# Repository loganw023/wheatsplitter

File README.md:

# wheatsplitter
This is a custom split ortholinear mechanical keyboard. I built this project to qualify for Outpost and to further my PCB, CAD, and coding skills. I was also interested in building this keyboard because I worked on Hackpad last summer, and wanted to continue building keyboard-type projects. This project taught me a lot about PCB design, especially since my last PCB was done in December. I also learned a lot about the specifics on how keyboard matrixes work, which was very interesting. 

## Schematic
Here is my schematic:

## PCB
Here is the PCB:

## CAD
Here is the CAD for the case:

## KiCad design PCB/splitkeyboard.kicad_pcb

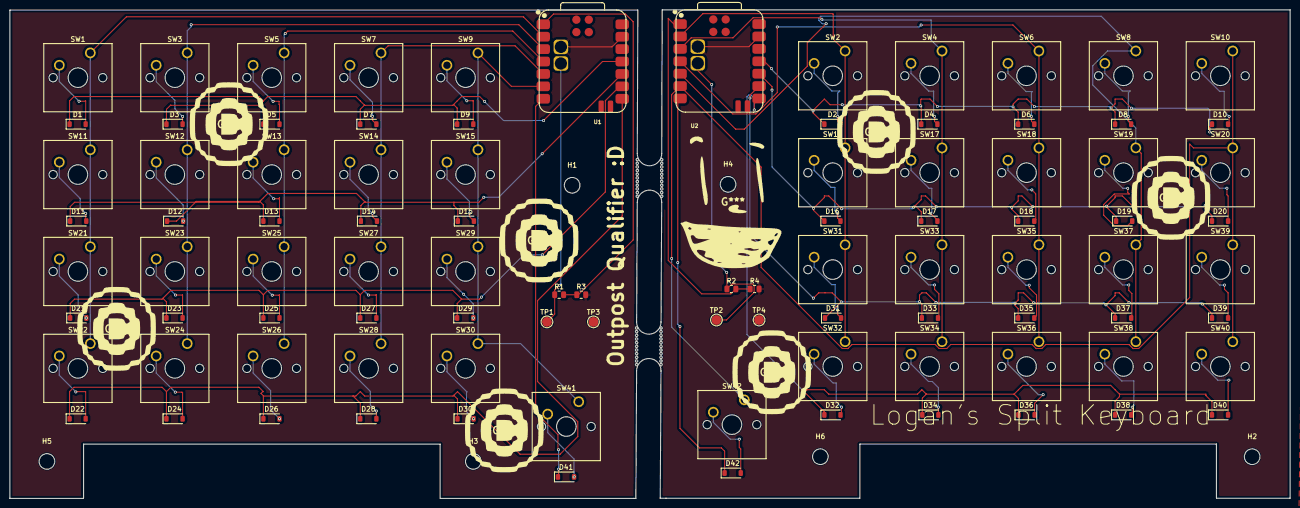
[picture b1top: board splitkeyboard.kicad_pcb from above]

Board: 2 copper layers, 262.1 x 100.0 mm, 102 parts (0 on the bottom side), 67 nets.

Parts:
D1, D2, D3, D4, D5, D6, D7, D8, D9, D10, D11, D12, D13, D14, D15, D16, D17, D18, D19, D20, D21, D22, D23, D24, D25, D26, D27, D28, D29, D30, D31, D32, D33, D34, D35, D36, D37, D38, D39, D40, D41, D42: D; D_SOD-123
H1, H2, H3, H4, H5, H6: MountingHole; MountingHole_3.2mm_M3
H4#2, H7: MountingHole; mouse-bite-5mm-slot
R1, R2: 806k; R_0805_2012Metric
R3, R4: 2M; R_0805_2012Metric
SW1, SW2, SW3, SW4, SW5, SW6, SW7, SW8, SW9, SW10, SW11, SW12, SW13, SW14, SW15, SW16, SW17, SW18, SW19, SW20, SW21, SW22, SW23, SW24, SW25, SW26, SW27, SW28, SW29, SW30, SW31, SW32, SW33, SW34, SW35, SW36, SW37, SW38, SW39, SW40, SW41, SW42: SW_Push; SW_Cherry_MX_1.00u_PCB
TP1, TP2, TP3, TP4: TestPoint; TestPoint_Pad_D2.0mm
U1, U2: XIAO-nRF52840-SMD; modified-XIAO-nRF52840-SMD

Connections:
/Left/BT_PIN: R1.2, R3.1, U1.1 (P0.02_A0_D0)
/Left/COL0: SW1.1, SW11.1, SW21.1, SW22.1, U1.2 (P0.03_A1_D1)
/Left/COL1: SW3.1, SW12.1, SW23.1, SW24.1, U1.3 (P0.28_A2_D2)
/Left/COL2: SW5.1, SW13.1, SW25.1, SW26.1, U1.4 (P0.29_A3_D3)
/Left/COL3: SW7.1, SW14.1, SW27.1, SW28.1, U1.5 (P0.04_A4_D4_SDA)
/Left/COL4: SW9.1, SW15.1, SW29.1, SW30.1, SW41.1, U1.6 (P0.05_A5_D5_SCL)
/Left/ROW0: D1.1 (K), D3.1 (K), D5.1 (K), D7.1 (K), D9.1 (K), U1.11 (P1.15_D10_MOSI)
/Left/ROW1: D11.1 (K), D12.1 (K), D13.1 (K), D14.1 (K), D15.1 (K), U1.10 (P1.14_D9_MISO)
/Left/ROW2: D21.1 (K), D23.1 (K), D25.1 (K), D27.1 (K), D29.1 (K), U1.9 (P1.13_D8_SCK)
/Left/ROW3: D22.1 (K), D24.1 (K), D26.1 (K), D28.1 (K), D30.1 (K), U1.8 (P1.12_D7_RX)
/Left/ROW4: D41.1 (K), U1.7 (P1.11_D6_TX)
/Left/VBAT: R1.1, TP1.1, U1.15 (BAT)
/Right/BT_PIN: R2.2, R4.1, U2.1 (P0.02_A0_D0)
/Right/COL0: SW2.1, SW16.1, SW31.1, SW32.1, U2.2 (P0.03_A1_D1)
/Right/COL1: SW4.1, SW17.1, SW33.1, SW34.1, U2.3 (P0.28_A2_D2)
/Right/COL2: SW6.1, SW18.1, SW35.1, SW36.1, U2.4 (P0.29_A3_D3)
/Right/COL3: SW8.1, SW19.1, SW37.1, SW38.1, U2.5 (P0.04_A4_D4_SDA)
/Right/COL4: SW10.1, SW20.1, SW39.1, SW40.1, SW42.1, U2.6 (P0.05_A5_D5_SCL)
/Right/ROW0: D2.1 (K), D4.1 (K), D6.1 (K), D8.1 (K), D10.1 (K), U2.11 (P1.15_D10_MOSI)
/Right/ROW1: D16.1 (K), D17.1 (K), D18.1 (K), D19.1 (K), D20.1 (K), U2.10 (P1.14_D9_MISO)
/Right/ROW2: D31.1 (K), D33.1 (K), D35.1 (K), D37.1 (K), D39.1 (K), U2.9 (P1.13_D8_SCK)
/Right/ROW3: D32.1 (K), D34.1 (K), D36.1 (K), D38.1 (K), D40.1 (K), U2.8 (P1.12_D7_RX)
/Right/ROW4: D42.1 (K), U2.7 (P1.11_D6_TX)
/Right/VBAT: R2.1, TP2.1, U2.15 (BAT)
GND: R3.2, R4.2, TP3.1, TP4.1, U1.13 (GND), U1.16 (GND), U2.13 (GND), U2.16 (GND)
unnamed: D1.2 (A), SW1.2
unnamed: D2.2 (A), SW2.2
unnamed: D3.2 (A), SW3.2
unnamed: D4.2 (A), SW4.2
unnamed: D5.2 (A), SW5.2
unnamed: D6.2 (A), SW6.2
unnamed: D7.2 (A), SW7.2
unnamed: D8.2 (A), SW8.2
unnamed: D9.2 (A), SW9.2
unnamed: D10.2 (A), SW10.2
unnamed: D11.2 (A), SW11.2
unnamed: D12.2 (A), SW12.2
unnamed: D13.2 (A), SW13.2
unnamed: D14.2 (A), SW14.2
unnamed: D15.2 (A), SW15.2
unnamed: D16.2 (A), SW16.2
unnamed: D17.2 (A), SW17.2
unnamed: D18.2 (A), SW18.2
unnamed: D19.2 (A), SW19.2
unnamed: D20.2 (A), SW20.2
unnamed: D21.2 (A), SW21.2
unnamed: D22.2 (A), SW22.2
unnamed: D23.2 (A), SW23.2
unnamed: D24.2 (A), SW24.2
unnamed: D25.2 (A), SW25.2
unnamed: D26.2 (A), SW26.2
unnamed: D27.2 (A), SW27.2
unnamed: D28.2 (A), SW28.2
unnamed: D29.2 (A), SW29.2
unnamed: D30.2 (A), SW30.2
unnamed: D31.2 (A), SW31.2
unnamed: D32.2 (A), SW32.2
unnamed: D33.2 (A), SW33.2
unnamed: D34.2 (A), SW34.2
unnamed: D35.2 (A), SW35.2
unnamed: D36.2 (A), SW36.2
unnamed: D37.2 (A), SW37.2
unnamed: D38.2 (A), SW38.2
unnamed: D39.2 (A), SW39.2
unnamed: D40.2 (A), SW40.2
unnamed: D41.2 (A), SW41.2
unnamed: D42.2 (A), SW42.2

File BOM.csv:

"Id";"Designator";"Footprint";"Quantity";"Designation";"Supplier and ref";
1;"SW19,SW25,SW22,SW8,SW32,SW14,SW21,SW16,SW30,SW35,SW3,SW29,SW13,SW38,SW23,SW17,SW39,SW2,SW10,SW37,SW34,SW12,SW24,SW15,SW5,SW7,SW26,SW18,SW33,SW1,SW9,SW40,SW20,SW6,SW27,SW36,SW28,SW42,SW31,SW41,SW4,SW11";"SW_Cherry_MX_1.00u_PCB";42;"SW_Push";;;
2;"D7,D10,D41,D4,D24,D21,D12,D42,D29,D16,D35,D3,D18,D15,D20,D40,D32,D5,D25,D6,D27,D39,D36,D17,D37,D30,D28,D2,D19,D11,D22,D8,D31,D13,D38,D9,D26,D34,D14,D1,D33,D23";"D_SOD-123";42;"D";;;
3;"R3,R4";"R_0805_2012Metric";2;"2M";;;
4;"TP4,TP3,TP1,TP2";"TestPoint_Pad_D2.0mm";4;"TestPoint";;;
5;"R2,R1";"R_0805_2012Metric";2;"806k";;;
6;"U2,U1";"modified-XIAO-nRF52840-SMD";2;"XIAO-nRF52840-SMD";;;

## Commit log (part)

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2026-06-30 Added all files for project
2026-06-30 Update README
2026-06-30 Update journal
2026-06-30 Update BOM
